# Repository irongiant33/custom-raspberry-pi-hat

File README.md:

# Raspberry Pi Hat

## Purpose

Create a hardware interface for the Raspberry Pi to enable toggling of 5 LEDs of different colors, some DC fans, and a 12V solenoid. 

## Demo

https://www.youtube.com/watch?v=JTKpwDRQpkI

## Board Layout

## Design Decisions

### Using subprocess to drive Raspberry Pi GPIO outputs LOW

I noticed some strange behavior when running an older version of `gpio_driver.py` when I did not have the `subprocess` module imported. When I would `CTRL+C` exit from the program, all of the GPIO outputs would drive high - resulting in charging the capacitor for the solenoid & driving all of the LED outputs high. To me, this was undesired behavior because I didn't want the bright LEDs to be on unless the "proposal program" was actively running. 

The best reasoning for why this happened was found on the Raspberry Pi Stack Exchange (https://raspberrypi.stackexchange.com/questions/121081/leds-do-not-turn-off-after-the-raspberry-pi-powers-down#:~:text=If%20you%20want%20to%20make%20sure%20all%20pins,%28set%20all%20pins%20to%20output%20and%20drive%20low%29.) where they reasoned that the operating system does this by default - this seems strange to me because the Pi could potentially have a short circuit and burn out the pins if it leaves them high.

Anyway, my solution to this was to use `subprocess` and the `raspi-gpio` script as suggested in the thread to force the outputs low. However, this results in a GPIO warning the next time `gpio_driver.py` is launched. To get around this, I just ignored the GPIO warnings.

### Push-button solenoid trigger and the one second trigger time

The two circled regions of the schematic show the RC timing circuit that keeps the pulse active. I chose to go for a time constant of 1s to enable the triggered pulse from either the Raspberry Pi or the manual switch two drive the output of the solenoid high. I decided to do this mainly for safety, but the one second was arbitrary. I observed that if the solenoid was kept in an active state for a prolonged period of time, it would begin to heat up (as well as Q11 in the schematic). To limit the dissipated power between 12V and ground, I decided to implement logic to allow for the solenoid to only trigger for 1 second at a time.

The drawback of this is that you must wait for C1 and C2 to charge back up before triggering the solenoid again. Theoretically, this should be at most one second as well, but I've observed that it is better to give it ~3 seconds to fully charge. 

## PCB Printing

Check out the "pcbway-09oct23" tag to see the updates I made to the schematic and the PCB in order to make it printable. I ended up going with PCBWay to print everything, I exported the KiCad PCB file to Gerber, zipped it up, and uploaded it to PCBWay for the print. Fingers crossed everything comes out okay! 

Here is how I phrased my previous "future work""

> This would be a fun opportunity to learn more about KiCad. They have a good basic tutorial here (https://docs.kicad.org/7.0/en/getting_started_in_kicad/getting_started_in_kicad.html) which was helpful to start playing with the PCB. Soldering the prototype board was a huge PITA and I was worried that I was going to mess something up. 
>
> One area I'd have to fix with the current KiCad files that are in this folder is the footprint for some of the components are off. I was just curious what the board layout would look like, but I would have to get the footprint for the resistors, capacitors, and pin headers to match up with what I have. It would be even better if I could match the Raspberry Pi footprint to effectively create a Raspberry Pi hat. 

I completely forgot about that old "getting started" guide, but thankfully remembered most everything I needed to in order to get things to work. With the help of my digital calipers, I updated the footprints of all of the devices in my schematic to match that which I had on hand. I also heavily leaned on Raspberry Pi's schematics and mechanical drawings (https://www.raspberrypi.com/documentation/computers/raspberry-pi.html#schematics-and-mechanical-drawings) for help in making it compatible for a Pi hat. I wanted to have room for the Boost converter that I had for amazon for everything to be really compact, and this made it a challenge to fit everything together - but it fit! That constraint definitely made the via routing more interesting, but I got it to work.

I ended up editing the width of the via for the power line (anything associated with 12V) to mimic the width of 22AWG cable - however, as I've noted on the new future work, it would have been better to make an electrical simulation to know exactly what I needed here. 

## Future Work

### KiCad improvements

- Ground plane printing
- Matching the 3D rendering model to what I have in real life
    - Making my own footprints and renderings
- leveraging community templates
- Better electrical simulation to better approximate track widths

### Implement the Cmd library for gpio_driver.py

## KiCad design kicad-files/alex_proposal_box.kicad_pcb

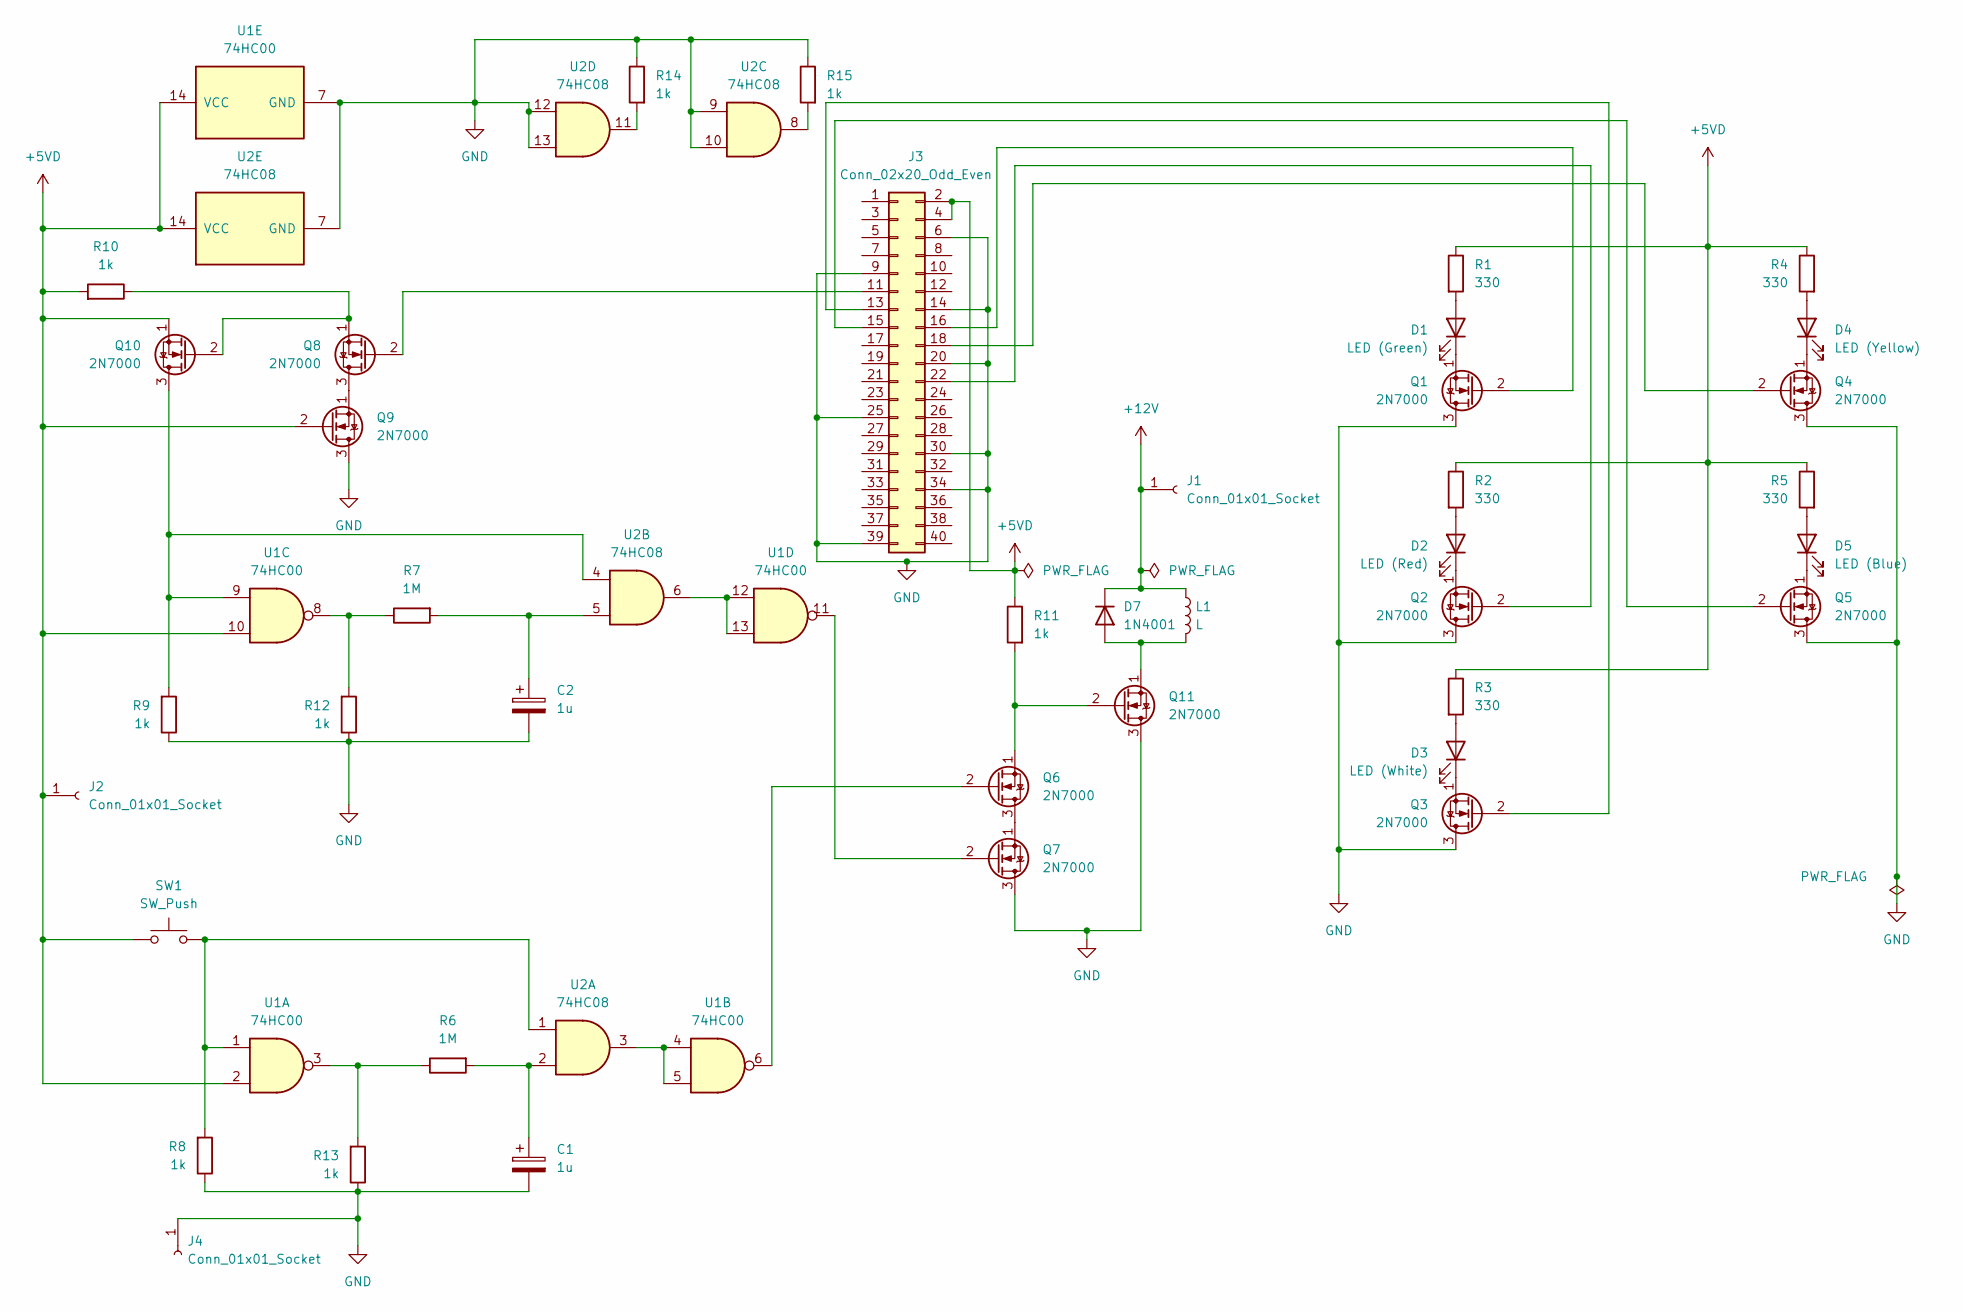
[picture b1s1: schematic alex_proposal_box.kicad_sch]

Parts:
C1, C2: 1u; CP_Radial_D5.0mm_P2.50mm
D1: LED (Green); D_DO-15_P2.54mm_Vertical_AnodeUp
D2: LED (Red); D_DO-15_P2.54mm_Vertical_AnodeUp
D3: LED (White); D_DO-15_P2.54mm_Vertical_AnodeUp
D4: LED (Yellow); D_DO-15_P2.54mm_Vertical_AnodeUp
D5: LED (Blue); D_DO-15_P2.54mm_Vertical_AnodeUp
D7: 1N4001; D_DO-41_SOD81_P10.16mm_Horizontal
J1, J2, J4: Conn_01x01_Socket; PinSocket_1x01_P2.00mm_Vertical
J3: Conn_02x20_Odd_Even; PinHeader_2x20_P2.54mm_Vertical
L1: L; L_Axial_L5.0mm_D3.6mm_P10.00mm_Horizontal_Murata_BL01RN1A2A2
Q1, Q2, Q3, Q4, Q5, Q6, Q7, Q8, Q9, Q10, Q11: 2N7000; TO-92_Inline
R1, R2, R3, R4, R5: 330; R_Axial_DIN0411_L9.9mm_D3.6mm_P12.70mm_Horizontal
R6, R7: 1M; R_Axial_DIN0411_L9.9mm_D3.6mm_P12.70mm_Horizontal
R8, R9, R10, R11, R12, R13, R14, R15: 1k; R_Axial_DIN0411_L9.9mm_D3.6mm_P12.70mm_Horizontal
SW1: SW_Push; SW_PUSH-6.5mm
U1: 74HC00; DIP-14_W7.62mm_Socket_LongPads
U2: 74HC08; DIP-14_W7.62mm_Socket_LongPads

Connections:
+5VD: J2.1, J3.2, J3.4, Q9.2 (G), Q10.1 (S), R1.1, R2.1, R3.1, R4.1, R5.1, R10.2, R11.1, SW1.1, U1.2, U1.10, U1.14 (VCC), U2.14 (VCC)
+12V: D7.1 (K), J1.1, L1.1
GND: C1.2, C2.2, J3.6, J3.9, J3.14, J3.20, J3.25, J3.30, J3.34, J3.39, J4.1, Q1.3 (D), Q2.3 (D), Q3.3 (D), Q4.3 (D), Q5.3 (D), Q7.3 (D), Q9.3 (D), Q11.3 (D), R8.1, R9.1, R12.1, R13.1, R14.1, R15.1, U1.7 (GND), U2.7 (GND), U2.9, U2.10, U2.12, U2.13
unnamed: C1.1, R6.2, U2.2
unnamed: C2.1, R7.2, U2.5
unnamed: D1.2 (A), R1.2
unnamed: D1.1 (K), Q1.1 (S)
unnamed: D2.2 (A), R2.2
unnamed: D2.1 (K), Q2.1 (S)
unnamed: D3.2 (A), R3.2
unnamed: D3.1 (K), Q3.1 (S)
unnamed: D4.2 (A), R4.2
unnamed: D4.1 (K), Q4.1 (S)
unnamed: D5.2 (A), R5.2
unnamed: D5.1 (K), Q5.1 (S)
unnamed: D7.2 (A), L1.2, Q11.1 (S)
unnamed: J3.11, Q8.2 (G)
unnamed: J3.13, Q3.2 (G)
unnamed: J3.15, Q5.2 (G)
unnamed: J3.16, Q1.2 (G)
unnamed: J3.18, Q4.2 (G)
unnamed: J3.22, Q2.2 (G)
unnamed: Q6.3 (D), Q7.1 (S)
unnamed: Q6.2 (G), U1.6
unnamed: Q7.2 (G), U1.11
unnamed: Q8.3 (D), Q9.1 (S)
unnamed: Q10.3 (D), R9.2, U1.9, U2.4
unnamed: Q8.1 (S), Q10.2 (G), R10.1
unnamed: Q6.1 (S), Q11.2 (G), R11.2
unnamed: R8.2, SW1.2, U1.1, U2.1
unnamed: R7.1, R12.2, U1.8
unnamed: R6.1, R13.2, U1.3
unnamed: R14.2, U2.11
unnamed: R15.2, U2.8
unnamed: U1.4, U1.5, U2.3
unnamed: U1.12, U1.13, U2.6

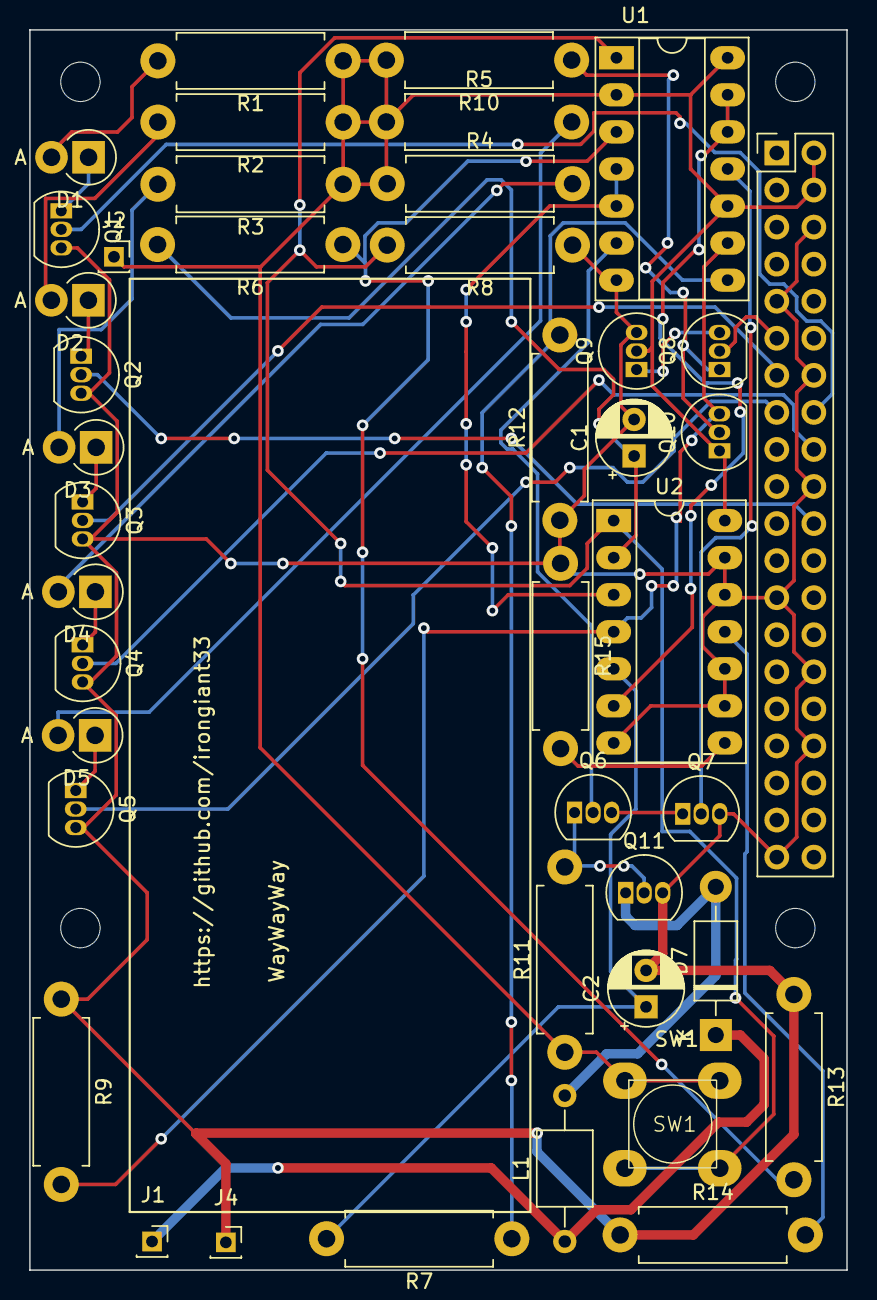
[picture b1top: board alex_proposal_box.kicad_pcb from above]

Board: 2 copper layers, 56.0 x 85.0 mm, 42 parts (0 on the bottom side), 36 nets.

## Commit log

2023-06-19 adding kicad files
2023-06-20 updating pcb layout
2023-06-20 adding example python script
2023-06-20 editing the gpio driver to make it slightly more Pythonic
2023-06-20 adding reasoning for 1 second pulse
2023-06-21 adding video and image of the circuit
2023-06-21 deleting gif since it is too large and linking to youtube video
2023-06-21 adding board layout and link to video demo
2023-10-09 made the schematic printable on a PCB
2023-10-09 adding video files to gitignore
2023-10-09 removing merge conflict artifact from readme
2023-10-09 editing future work section to reflect new PCB improvements
